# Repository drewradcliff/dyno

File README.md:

# Dyno

Dyno is an open-source finger-strength dynamometer. The project combines a
custom load-cell PCB, firmware for a Seeed Studio XIAO ESP32C3, and a mobile
app that displays force measurements over Bluetooth Low Energy.

## Repository

- [`hardware/`](hardware/) — KiCad schematic, PCB, and project-local libraries
- [`firmware/`](firmware/) — ESP32C3 firmware, calibration, and telemetry
- [`mobile/`](mobile/) — Expo/React Native companion app

The project is under active development. The PCB is currently an unverified
prototype and should be reviewed before fabrication.

## License

Original project work is licensed under the [MIT License](LICENSE). Third-party
components retain their upstream licenses and are attributed in the relevant
component directories.

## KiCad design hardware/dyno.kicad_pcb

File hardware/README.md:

# Dyno hardware

KiCad design for the battery-powered Dyno finger-strength sensor. The board
combines a Seeed Studio XIAO ESP32C3 with an HX711 ADC and an external load
cell.

> **Status:** early, unverified prototype. The schematic and PCB have not yet
> been validated on manufactured hardware.

The [`production`](production) directory contains the JLCPCB Gerbers, BOM, and
placement data generated by KiCad's Fabrication Toolkit.

## Open the project

Open [`dyno.kicad_pro`](dyno.kicad_pro) with KiCad 10 or newer.

## Attribution and licensing

The original Dyno hardware design is licensed under the repository's
[MIT License](../LICENSE).

The vendored Seeed Studio XIAO KiCad libraries were created by Seeed Studio and
community contributors and are licensed separately under CC BY-SA 4.0. See
[`libraries/README.md`](libraries/README.md) and
[`libraries/LICENSE-CC-BY-SA-4.0.md`](libraries/LICENSE-CC-BY-SA-4.0.md).

The design also uses symbols and footprints from the official KiCad libraries,
which are distributed under CC BY-SA 4.0 with the KiCad libraries exception.
That exception permits their use in electronic designs without requiring the
design itself to adopt CC BY-SA.

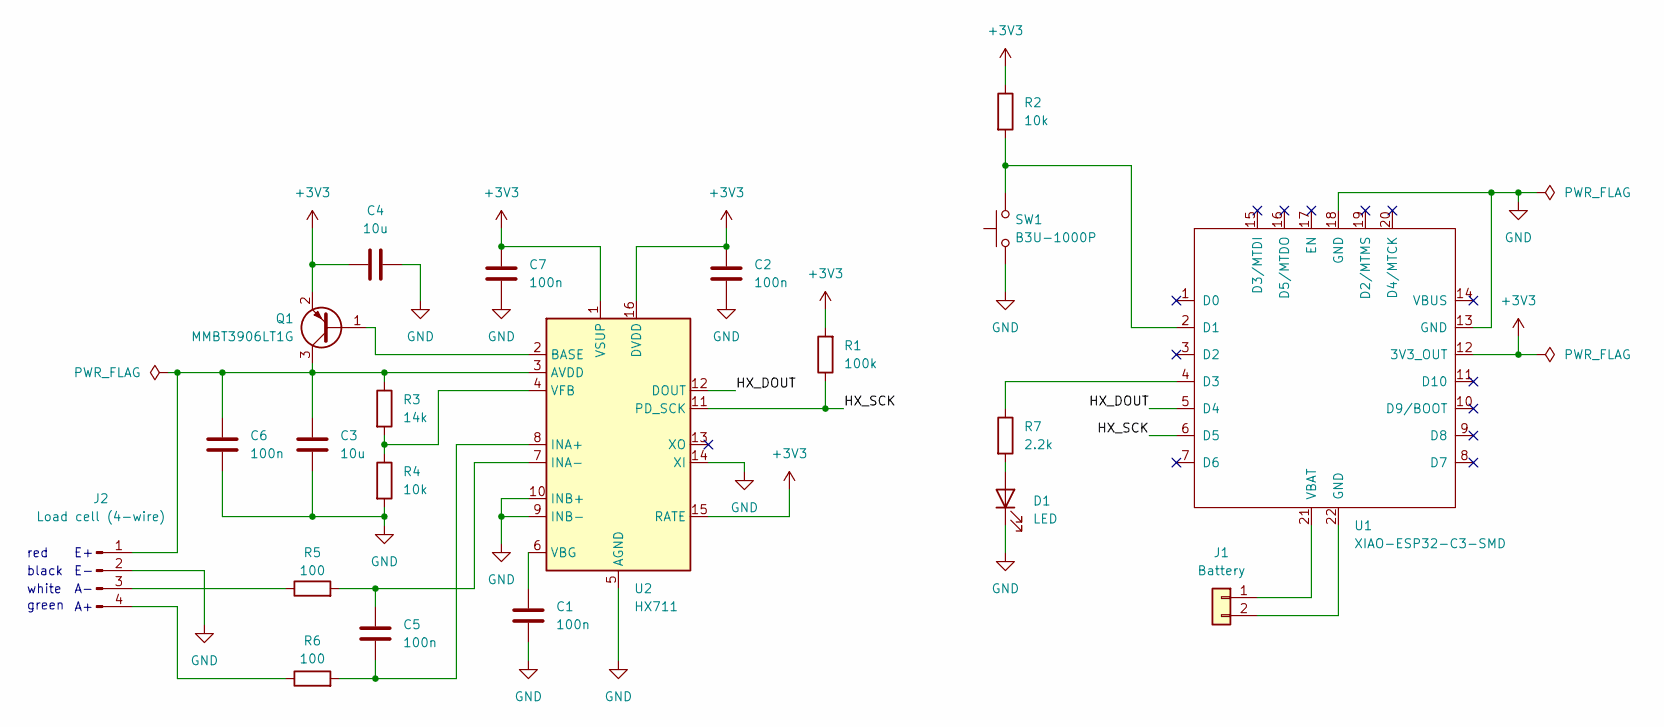
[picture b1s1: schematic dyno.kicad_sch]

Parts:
C1, C2, C5, C6, C7: 100n; C_0603_1608Metric; MPN CC0603KRX7R9BB104; JLCPCB Part # C14663
C3, C4: 10u; C_0805_2012Metric; MPN CL21A106KAYNNNE; JLCPCB Part # C15850
D1: LED; LED_0603_1608Metric; MPN KT-0603R; JLCPCB Part # C2286
J1: Battery; JST_PH_S2B-PH-SM4-TB_1x02-1MP_P2.00mm_Horizontal; MPN S2B-PH-SM4-TB(LF)(SN); JLCPCB Part # C295747
J2: Load cell (4-wire); JST_SH_SM04B-SRSS-TB_1x04-1MP_P1.00mm_Horizontal; MPN SM04B-SRSS-TB(LF)(SN); JLCPCB Part # C160404
Q1: MMBT3906LT1G; SOT-23; MPN MMBT3906LT1G; JLCPCB Part # C53444
R1: 100k; R_0603_1608Metric; MPN 0603WAF1003T5E; JLCPCB Part # C25803
R2, R4: 10k; R_0603_1608Metric; MPN 0603WAF1002T5E; JLCPCB Part # C25804
R3: 14k; R_0603_1608Metric; MPN 0603WAF1402T5E; JLCPCB Part # C22803
R5, R6: 100; R_0603_1608Metric; MPN 0603WAF1000T5E; JLCPCB Part # C22775
R7: 2.2k; R_0603_1608Metric; MPN 0603WAF2201T5E; JLCPCB Part # C4190
SW1: B3U-1000P; SW_SPST_B3U-1000P; MPN B3U-1000P; JLCPCB Part # C231329
U1: XIAO-ESP32-C3-SMD; MPN 113991054; JLCPCB Part # C18212168
U2: HX711; SOIC-16_3.9x9.9mm_P1.27mm; MPN HX711; JLCPCB Part # C6705483

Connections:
+3V3: C2.2, C4.1, C7.2, Q1.2 (E), R1.2, R2.1, U1.12 (3V3_OUT), U2.1 (VSUP), U2.15 (RATE), U2.16 (DVDD)
/HX_DOUT: U1.5 (D4), U2.12 (DOUT)
/HX_SCK: R1.1, U1.6 (D5), U2.11 (PD_SCK)
GND: C1.2, C2.1, C3.2, C4.2, C6.2, C7.1, D1.1 (K), J2.2, R4.2, SW1.1, U1.13 (GND), U1.18 (GND), U2.5 (AGND), U2.9 (INB-), U2.10 (INB+), U2.14 (XI)
unnamed: D1.2 (A), R7.2
unnamed: J1.1, U1.21 (VBAT)
unnamed: J1.2, U1.22 (GND)
unnamed: C3.1, C6.1, J2.1, Q1.3 (C), R3.1, U2.3 (AVDD)
unnamed: J2.3, R5.1
unnamed: J2.4, R6.1
unnamed: Q1.1 (B), U2.2 (BASE)
unnamed: R2.2, SW1.2, U1.2 (D1)
unnamed: R7.1, U1.4 (D3)
unnamed: C5.2, R6.2, U2.8 (INA+)
unnamed: C5.1, R5.2, U2.7 (INA-)
unnamed: C1.1, U2.6 (VBG)
unnamed: R3.2, R4.1, U2.4 (VFB)

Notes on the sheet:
green
red
white
black

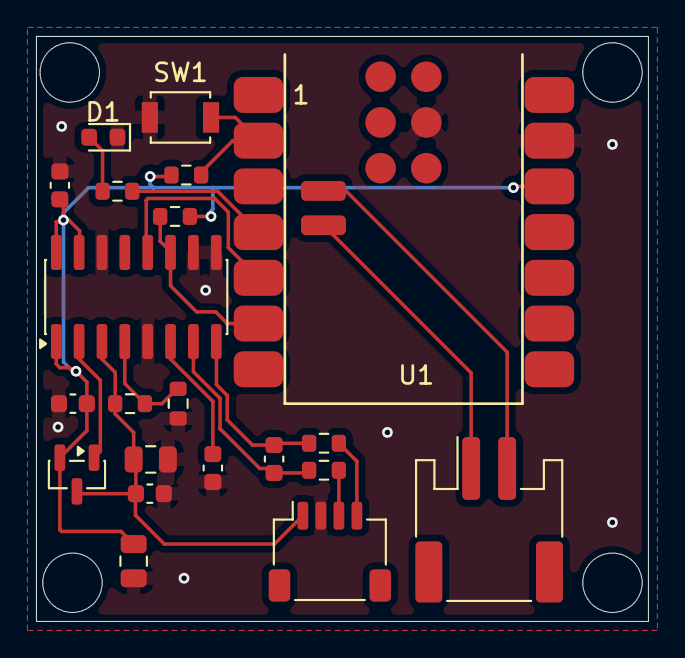
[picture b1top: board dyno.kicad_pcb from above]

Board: 2 copper layers, 34.0 x 32.5 mm, 21 parts (0 on the bottom side), 17 nets.

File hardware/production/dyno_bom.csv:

Designator,Footprint,Quantity,Value,LCSC Part #
"C1, C2, C5, C6, C7",0603,5,100n,C14663
"C3, C4",0805,2,10u,C15850
D1,0603,1,LED,C2286
J1,JST_PH_S2B-PH-SM4-TB_1x02-1MP_P2.00mm_Horizontal,1,Battery,C295747
J2,JST_SH_SM04B-SRSS-TB_1x04-1MP_P1.00mm_Horizontal,1,Load cell (4-wire),C160404
Q1,SOT-23,1,MMBT3906LT1G,C53444
R1,0603,1,100k,C25803
"R2, R4",0603,2,10k,C25804
R3,0603,1,14k,C22803
"R5, R6",0603,2,100,C22775
R7,0603,1,2.2k,C4190
SW1,SW_SPST_B3U-1000P,1,B3U-1000P,C231329
U1,XIAO-ESP32-C3-SMD,1,XIAO-ESP32-C3-SMD,C18212168
U2,SOIC-16_3.9x9.9mm_P1.27mm,1,HX711,C6705483
